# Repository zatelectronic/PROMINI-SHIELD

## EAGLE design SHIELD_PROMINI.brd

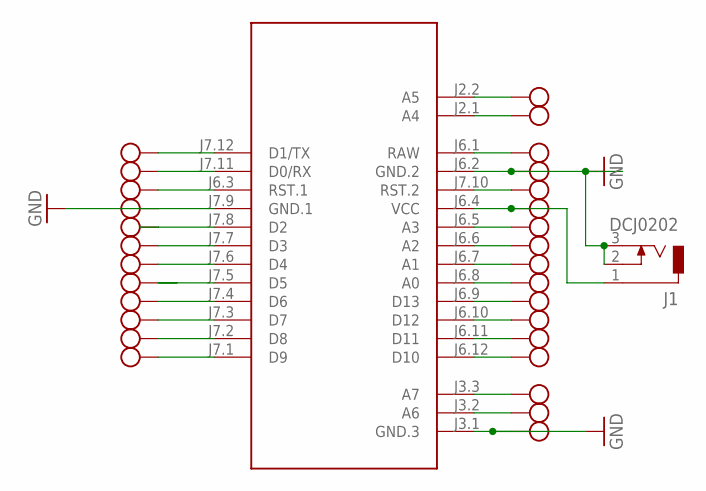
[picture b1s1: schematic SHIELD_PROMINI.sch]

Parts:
J1: DCJ0202
M1: ARDUINO-PRO-MINI-5.0V#NP; ARDUINO-PRO-MINI#NP
X1, X2: AK300/12
X3: AK300/5

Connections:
GND: J1.2, J1.3, M1.J3.1 (GND.3), M1.J6.2 (GND.2), M1.J7.9 (GND.1), X1.9, X2.2, X3.3
unnamed: M1.J7.12 (D1/TX), X1.12
unnamed: M1.J7.11 (D0/RX), X1.11
unnamed: M1.J7.4 (D6), X1.4
unnamed: M1.J7.2 (D8), X1.2
unnamed: M1.J7.8 (D2), X1.8
unnamed: M1.J7.7 (D3), X1.7
unnamed: M1.J7.6 (D4), X1.6
unnamed: M1.J7.5 (D5), X1.5
unnamed: M1.J7.3 (D7), X1.3
unnamed: M1.J7.1 (D9), X1.1
unnamed: M1.J7.10 (RST.2), X1.10
unnamed: M1.J6.1 (RAW), X2.1
unnamed: M1.J6.3 (RST.1), X2.3
unnamed: J1.1, M1.J6.4 (VCC), X2.4
unnamed: M1.J6.5 (A3), X2.5
unnamed: M1.J6.6 (A2), X2.6
unnamed: M1.J6.7 (A1), X2.7
unnamed: M1.J6.8 (A0), X2.8
unnamed: M1.J6.9 (D13), X2.9
unnamed: M1.J6.10 (D12), X2.10
unnamed: M1.J6.11 (D11), X2.11
unnamed: M1.J6.12 (D10), X2.12
unnamed: M1.J2.2 (A5), X3.5
unnamed: M1.J2.1 (A4), X3.4
unnamed: M1.J3.2 (A6), X3.2
unnamed: M1.J3.3 (A7), X3.1

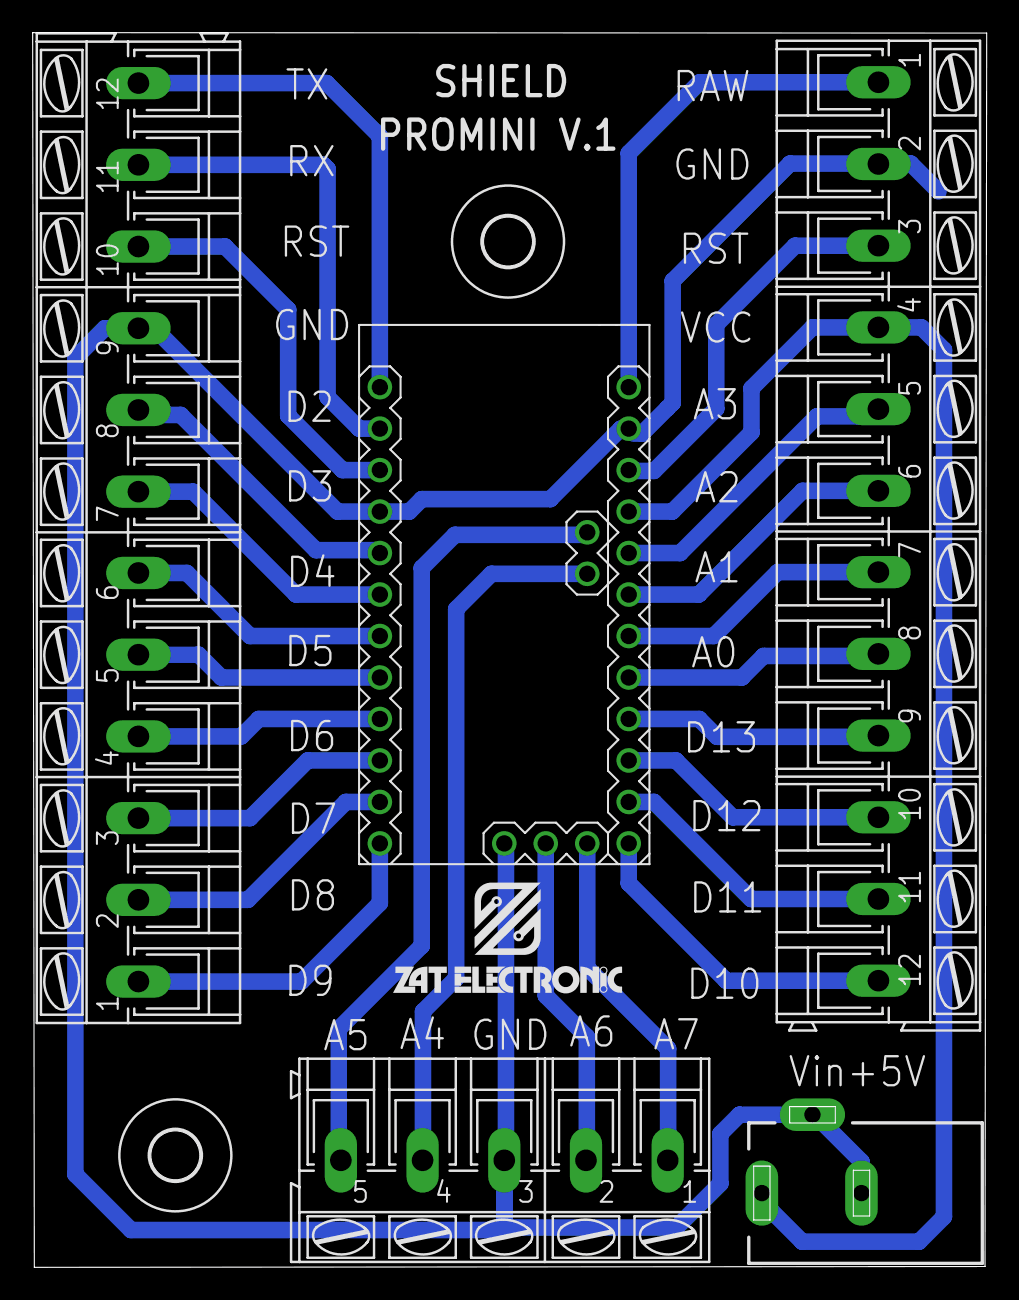
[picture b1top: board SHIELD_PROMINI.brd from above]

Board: 2 copper layers, 58.4 x 75.6 mm, 8 parts (0 on the bottom side), 27 nets.

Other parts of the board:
U$1: ZAT_ESCRITA_0.5
U$2, U$3: 3,0

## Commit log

2021-10-24 PRIMEIRO ENVIO
2021-10-25 ATUALIZAÇÃO
2021-11-27 ENVIO 2

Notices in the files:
parts and their libraries:
diy-modules: Released under the Creative Commons Attribution 4.0 International License: http://creativecommons.org/licenses/by/4.0
